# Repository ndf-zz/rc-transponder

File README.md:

# rc-transponder

RC Transponder Documentation

The Tag Heuer/Chronelec RC transponder is a
discontinued LF/HF magnetic induction type
identifier for sports timing applications. 

This repository contains information on the
transponder hardware as well as tools for
updating the firmware.

## Contents

   - [hardware](hardware/) : RC hardware reference
   - [firmware](firmware/) : Firmware information and analysis
   - [programmer](programmer/) : Firmware re-programmer and drill template
   - [scripts](scripts/) : Shell and python scripts
   - [altfw](altfw/) : Alternative firmware

## Overview

Based around the PIC16F639 Microcontroller with
Low-Frequency Analog Front-End, the RC transponder
works like a Passive Keyless Entry (PKE) device. 
It receives activation messages on 125kHz
and then responds with a numeric ID by repeating
differential pulse position encoded strings on 3.28MHz
for a short while.

Both LF and HF circuits are magnetically communicated
with a compatible Chronelec Protime decoder and loop.

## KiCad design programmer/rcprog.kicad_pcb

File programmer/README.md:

# Transponder Programmer

ICSP breakout board for re-programming RC transponders, KiCad 6
project.

## Transponder Preparation

Before re-programming, ICSP programming pads need to
be exposed by removing a small amount of the potting
compound with a white 1.5 mm diameter ferrule.

Use the "drill" template on a spare programmer PCB
to position the transponder and hold it square.
Then flip the assembly over and push ferrules into
the potting compound with a soldering iron
on low to medium heat.

Allow ferrules to cool, then carefully remove from assembly
exposing the programming pads.

After programming, pads can be left open for indoor use, or
filled with silicone for outdoor use.

## Programming

Place transponder carefully over programming pins
and then depress against pcb.

Run ipecmd or rcpatch script to update transponder as required.
If ipecmd fails with a connection error, check pad holes are
clear and aligned properly with programming pins. Gentle
rotation of the transponder while depressing it against the pcb
may help slightly misaligned pads make contact. Pad holes can be
enlarged with a red 2.0 mm diameter ferrule to help correct
misalignment.

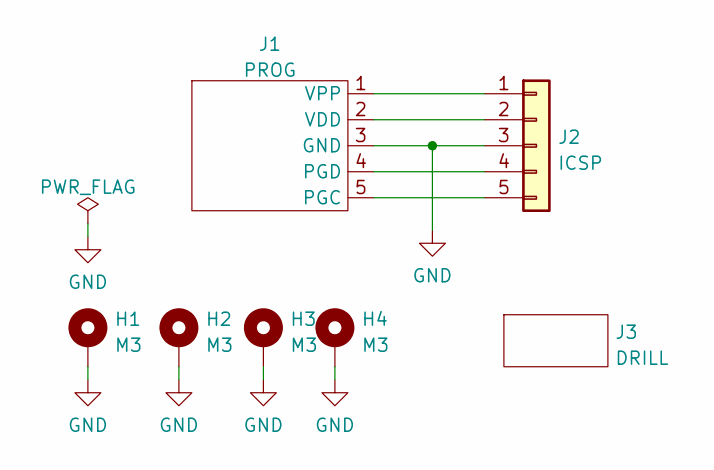
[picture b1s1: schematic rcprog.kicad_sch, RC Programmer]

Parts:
H1, H2, H3, H4: M3; MountingHole_3.2mm_M3_Pad
J1: PROG; progpins
J2: ICSP; PinHeader_1x05_P2.54mm_Horizontal
J3: DRILL; drillpins

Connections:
GND: H1.1, H2.1, H3.1, H4.1, J1.3 (GND), J2.3
unnamed: J1.1 (VPP), J2.1
unnamed: J1.2 (VDD), J2.2
unnamed: J1.4 (PGD), J2.4
unnamed: J1.5 (PGC), J2.5

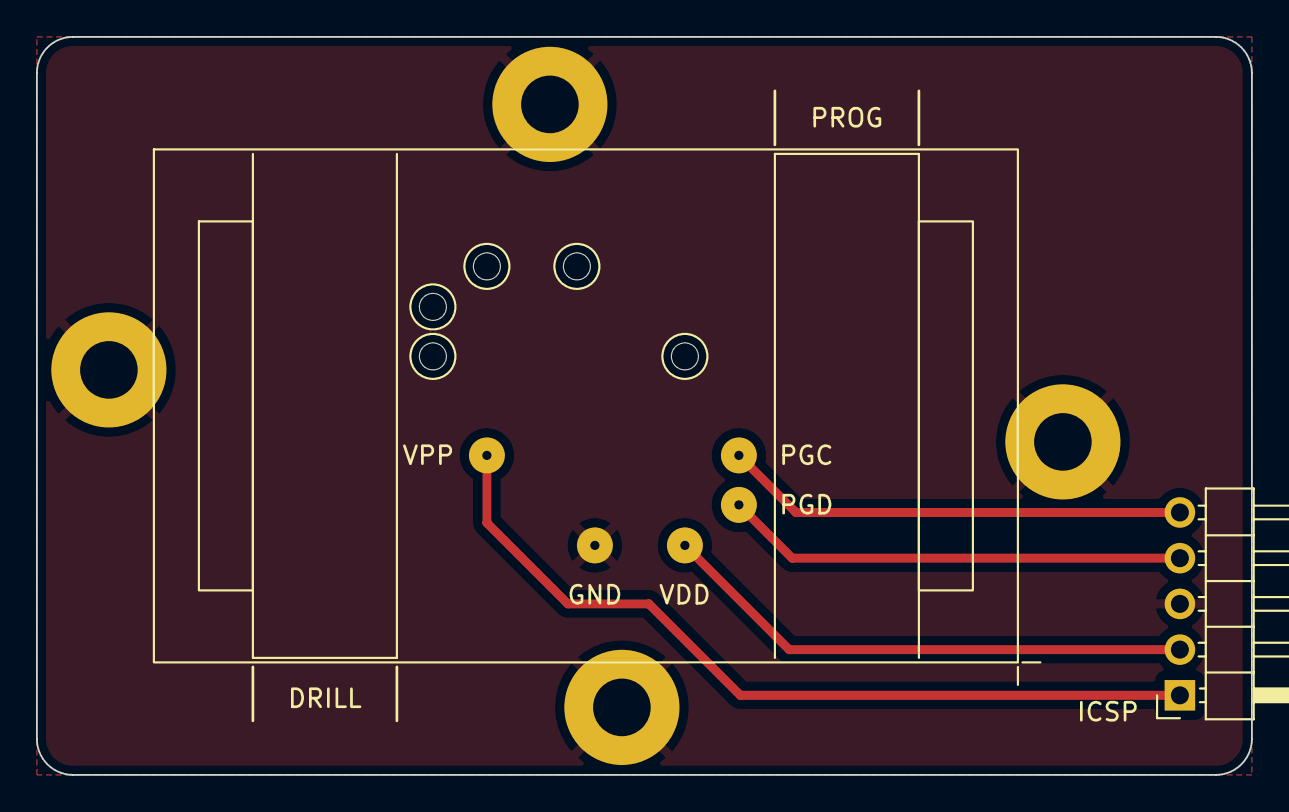
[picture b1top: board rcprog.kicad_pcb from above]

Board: 2 copper layers, 67.5 x 41.0 mm, 7 parts (0 on the bottom side), 5 nets.

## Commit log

2024-08-28 Add ipecmd shell wrapper
2024-08-30 Add transponder patch scripts
2024-08-31 Add RC firmware and annotated listing
2024-09-02 Include ID locations in firmware update
2024-09-02 Document road/track difference
2024-09-02 Add programmer PCB layout
2024-09-02 Document parity error check
2024-09-03 Add transponder preparation instruction
2024-09-03 Add variable and flag labels
2024-09-04 Add firmware pseudocode
2024-09-04 Add hardware info
2024-09-05 Add hardware measurements
2024-09-05 Fix image file typos
2024-09-05 Fix typo
2024-09-06 Add lfmon test program
2024-09-06 Fix typo in annotated listing
2024-09-09 Add message format documentation
2024-09-10 Set LFMon LED blink time to 1ms, clean up code slightly
2024-09-11 Add prolonged activation measurement
2024-09-11 Add gputils and vim ignores
2024-09-11 Update scripts to generate ID block
2024-09-11 Update test programs and add Makefile
2024-09-11 Add DISC alt firmware outline
2024-09-12 Find ID block using movwf instructions
2024-09-13 Add dtrn alt firmware
2024-09-13 Adjust timer schedule to handle more concurrent wakeups
2024-09-13 Improve low voltage detect and handle oscillator failure
2024-09-14 Enable BOD while not sleeping
2024-09-15 Init LFSR with low bits from ID number
